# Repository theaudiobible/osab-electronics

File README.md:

## OSAB - the Open Source Audio Bible player
## [theaudiobible.org](http://theaudiobible.org/)
#### Copyright (C) 2011-2022 Theophilus

OSAB is a design for a portable audio Bible player released under the MIT Licence in the hope that it will be used by others worldwide to produce and distribute portable audio players that are specifically designed to share God's word with those who need to hear.

The intention is to share firmware, software, schematics, PCB layout and enclosure design along with instructions on how to put it all together.  The intention with the enclosure is that it be 3D-printable on a low cost FDM 3D printer, or mass-producible via injection moulding.

## osab-electronics
This is the repository for the EDA files for OSAB.

### Dependencies
- The schematic and PCB design tool is [KiCad](http://kicad.org/)
- [meshconv](https://www.patrickmin.com/meshconv/) is used to convert the VRML file to STL for use in OpenSCAD for the enclosure design.

### Generate STL file
To generate `osab.stl` for inclusion in the `osab-enclosure/osab.stl` soft link:
1. Open `osab.kicad_pcb` in KiCad Pcbnew.
2. Click `File` > `Export` > `VRML`.
3. Set these options:
   - `Coordinate origin options`: `User defined origin`
   - `User defined origin`:
      - `Units`: `mm`
      - `X`: `150`
      - `Y`: `100`
   - `VRML Units for Output Files`: `mm`
4. Click `OK`.  The output file should be `osab.wrl`.
5. Quit Pcbnew.
6. Download `meshconv` from https://www.patrickmin.com/meshconv/
7. Put meshconv somewhere in your PATH:
   `sudo chown root.root meshconv`
   `sudo chmod 755 meshconv`
   `sudo mv meshconv /usr/local/bin`
8. Convert the VRML file to STL as follows:
   `meshconv osab.wrl -c stl`
9. The output file `osab.stl` should be in the `osab-electronics` directory - there is a soft link from `osab-enclosure/osab.stl` to this file for inclusion in `osab-enclosure/osab-enclosure.scad`.

### Licence
This is open source hardware released under the MIT Licence - please see the LICENCE file in this directory.

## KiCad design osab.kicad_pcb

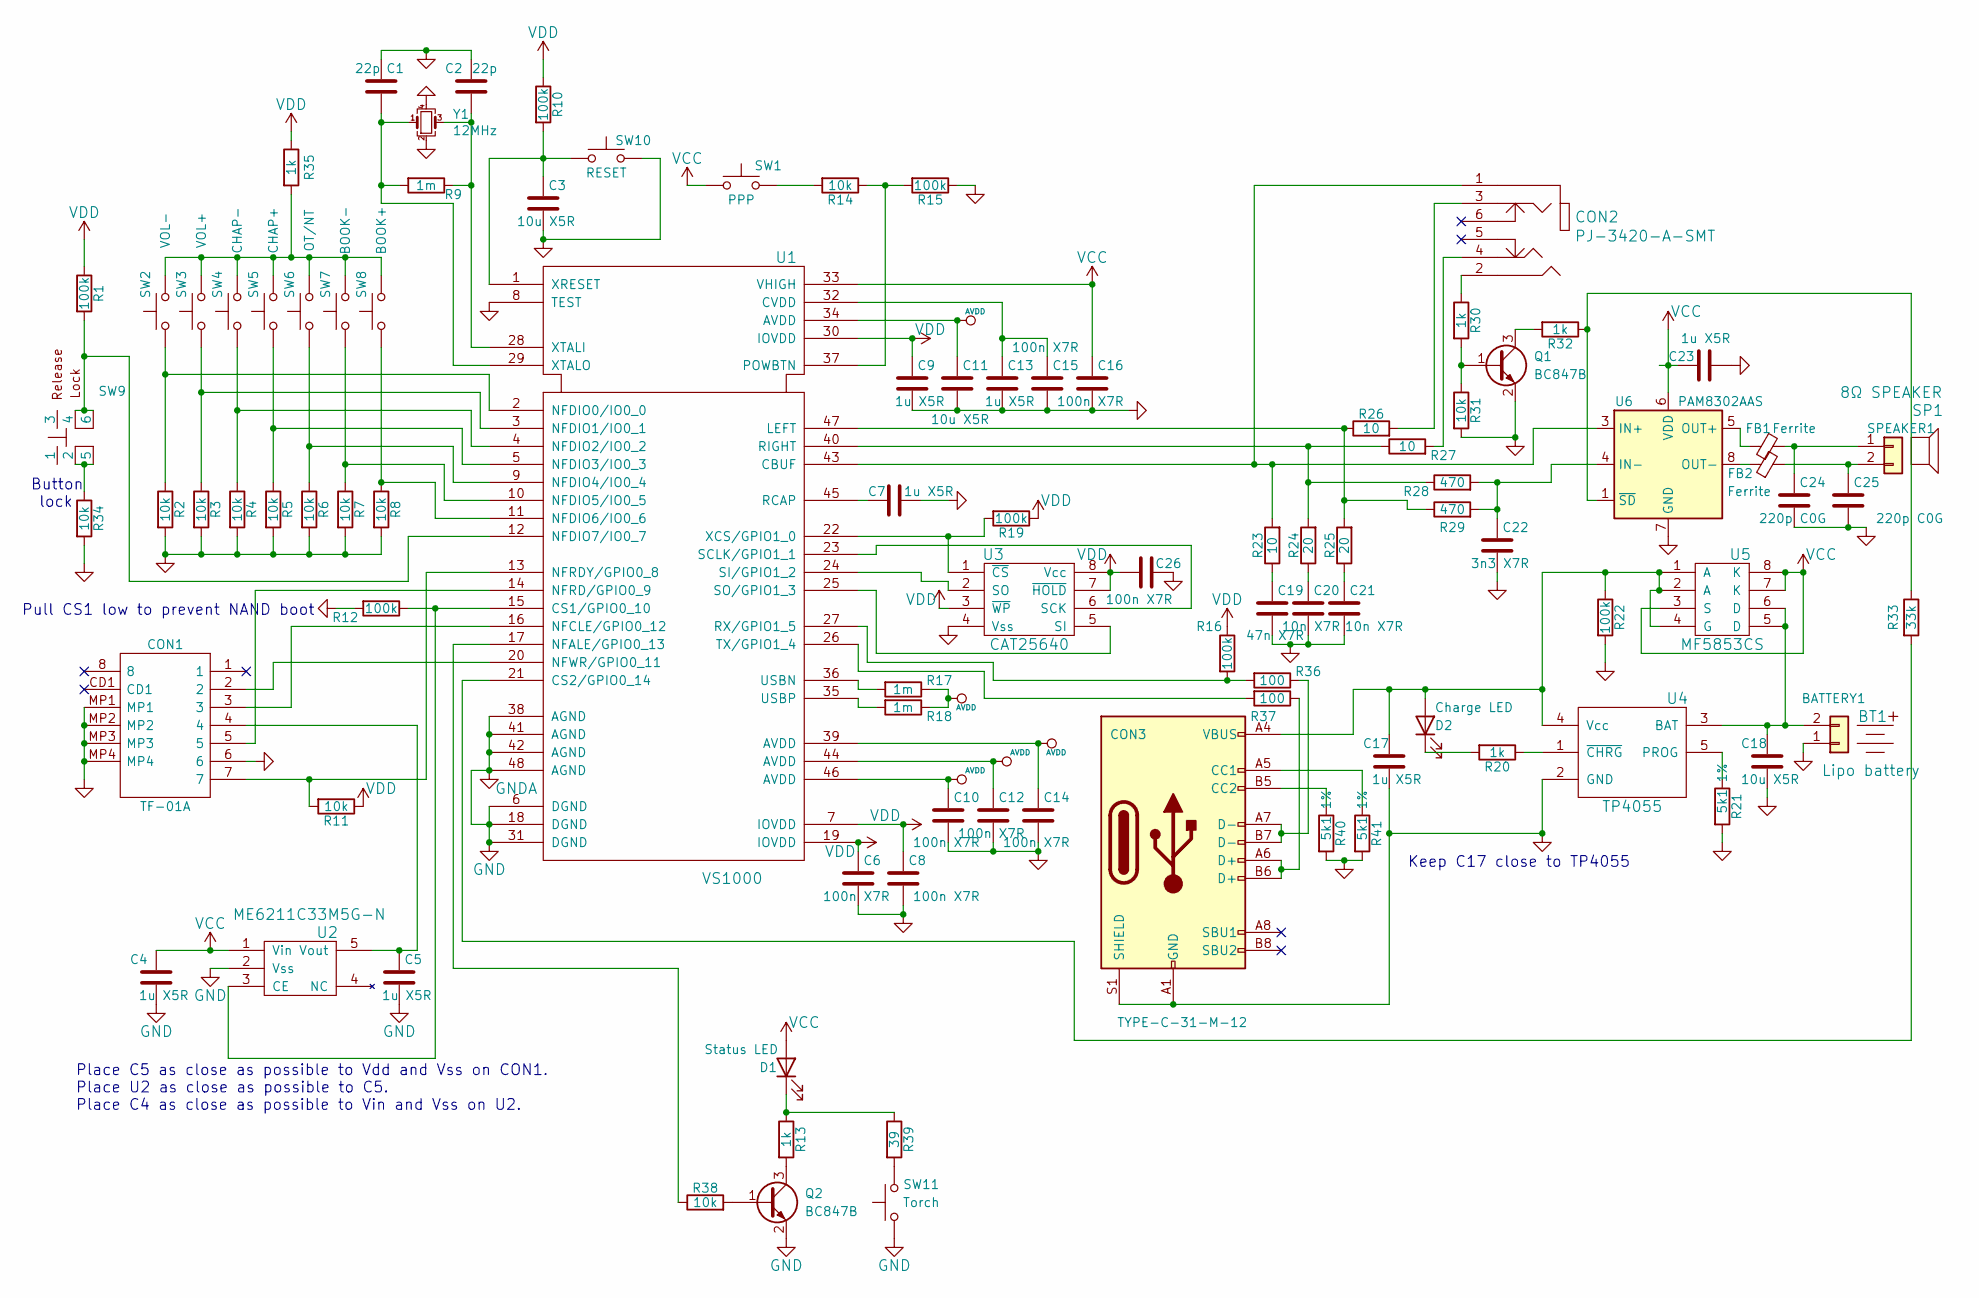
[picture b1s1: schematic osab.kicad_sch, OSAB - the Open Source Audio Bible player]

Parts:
BATTERY1: Conn_01x02; JST_PH_S2B-PH-SM4-TB_1x02-1MP_P2.00mm_Horizontal; MPN KH-A2001WF-02A; LCSC C2688784
BT1: Lipo battery; NULL; MPN BZ 602030
C1, C2: 22p; C_0603_1608Metric; MPN CL10C220JB8NNNC; LCSC C1653
C3, C11, C18: 10u X5R; C_0603_1608Metric; MPN CL10A106KP8NNNC; LCSC C19702
C4, C5, C7, C9, C13, C17, C23: 1u X5R; C_0603_1608Metric; MPN CL10A105KB8NNNC; LCSC C15849
C6, C8, C10, C12, C14, C15, C16, C26: 100n X7R; C_0603_1608Metric; MPN CL10B104KB8NNNC; LCSC C1591
C19: 47n X7R; C_0603_1608Metric; MPN CL10B473KB8NNNC; LCSC C1622
C20, C21: 10n X7R; C_0603_1608Metric; MPN CL10B103KB8NNNC; LCSC C1589
C22: 3n3 X7R; C_0603_1608Metric; MPN CL10B332KB8NNNC; LCSC C1613
C24, C25: 220p C0G; C_0603_1608Metric; MPN CL10C221JB8NNNC; LCSC C27675
CON1: TF-01A; TF01A; Manufacturer_Part_Number TF-01A; LCSC C91145
CON2: PJ-3420-A-SMT; MPN PJ-3420-A-SMT; LCSC C319102
CON3: TYPE-C-31-M-12; USB_C_Receptacle_HRO_TYPE-C-31-M-12; MPN TYPE-C-31-M-12; LCSC C165948
D1: Status LED; 0805-LED; MPN MHS171WDT-C2; LCSC C693902
D2: Charge LED; 0602-LED; MPN LTST-S270KRKT; LCSC C125114
FB1, FB2: Ferrite; R_0603_1608Metric; MPN MMZ1608Y152BTA00; LCSC C275454
Q1, Q2: BC847B; SOT-23; MPN BC847BLT1G; LCSC C94393
R1, R10, R12, R15, R16, R19, R22: 100k; R_0603_1608Metric; MPN ARG03FTC1003; LCSC C217682
R2, R3, R4, R5, R6, R7, R8, R11, R14, R31, R34, R38: 10k; R_0603_1608Metric; MPN ARG03FTC1002; LCSC C217687
R9, R17, R18: 1m; R_0603_1608Metric; MPN AR03FTC1004; LCSC C234360
R13, R20, R30, R32, R35: 1k; R_0603_1608Metric; MPN ARG03FTC1001; LCSC C217840
R21, R40, R41: 5k1 1%; R_0603_1608Metric; MPN ARG03FTC5101; LCSC C218090
R23, R26, R27: 10; R_0603_1608Metric; MPN ARG03FTC0100; LCSC C217691
R24, R25: 20; R_0603_1608Metric; MPN ARG03FTC0200; LCSC C217873
R28, R29: 470; R_0603_1608Metric; MPN ARG03FTC4700; LCSC C218042
R33: 33k; R_0603_1608Metric; MPN ARG03FTC3302; LCSC C217971
R36, R37: 100; R_0603_1608Metric; MPN ARG03FTC1000; LCSC C217683
R39: 39; R_0603_1608Metric; MPN 0603WAF390JT5E; LCSC C23154
SP1: 8Ω SPEAKER; NULL; MPN 28M03-8T-H52-L70; LCSC C391017
SPEAKER1: Conn_01x02; WAFER-125W-2P; MPN WAFER-125W-2P; LCSC C2840410
SW1: PPP; SW_SPST_TL3342; MPN K2-1187SQ-A4SW-06; LCSC C92584
SW2: VOL-; SW_SPST_TL3342; MPN K2-1187SQ-A4SW-06; LCSC C92584
SW3: VOL+; SW_SPST_TL3342; MPN K2-1187SQ-A4SW-06; LCSC C92584
SW4: CHAP-; SW_SPST_TL3342; MPN K2-1187SQ-A4SW-06; LCSC C92584
SW5: CHAP+; SW_SPST_TL3342; MPN K2-1187SQ-A4SW-06; LCSC C92584
SW6: OT/NT; SW_SPST_TL3342; MPN K2-1187SQ-A4SW-06; LCSC C92584
SW7: BOOK-; SW_SPST_TL3342; MPN K2-1187SQ-A4SW-06; LCSC C92584
SW8: BOOK+; SW_SPST_TL3342; MPN K2-1187SQ-A4SW-06; LCSC C92584
SW9: XKB5858-Z-F; MPN XKB5858-Z-F; LCSC C780036
SW10: RESET; SW_SPST_TL3342; MPN K2-1187SQ-A4SW-06; LCSC C92584
SW11: Torch; SW_SPST_TL3342; MPN K2-1187SQ-A4SW-06; LCSC C92584
U1: VS1000; LQFP-48_7x7mm_P0.5mm; MPN VS1000D-L; LCSC C486305
U2: ME6211C33M5G-N; SOT-23-5; MPN ME6211C33M5G-N; LCSC C82942
U3: CAT25640; SOIC-8_3.9x4.9mm_P1.27mm; MPN CAT25640VI-GT3; LCSC C153776
U4: TP4055; SOT-23-5; MPN TP4055; LCSC C28441
U5: MF5853CS; DFN8-2x3-0.65pitch; MPN MF5853CS; LCSC C375698
U6: PAM8302AAS; MSOP-8_3x3mm_P0.65mm; MPN PAM8302AASCR; LCSC C113367
Y1: 12MHz; Crystal_SMD_3225-4Pin_3.2x2.5mm; MPN X322512MSB4SI; LCSC C9002

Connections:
AVDD: C10.1, C11.1, C12.1, C14.1, R17.1, R18.1, U1.34 (AVDD), U1.39 (AVDD), U1.44 (AVDD), U1.46 (AVDD)
GND: BATTERY1.1, C1.1, C2.1, C3.2, C4.2, C5.2, C6.2, C7.1, C8.2, C9.2, C10.2, C11.2, C12.2, C13.2, C14.2, C15.2, C16.2, C17.2, C18.2, C19.2, C20.2, C21.2, C22.2, C23.2, C24.2, C25.2, C26.2, CON1.6, CON1.MP1, CON1.MP2, CON1.MP3, CON1.MP4, CON3.A1 (GND), CON3.A12 (GND), CON3.B1 (GND), CON3.B12 (GND), CON3.S1 (SHIELD), Q1.2 (E), Q2.2 (E), R2.2, R3.2, R4.2, R5.2, R6.2, R7.2, R8.2, R12.2, R15.1, R21.2, R22.2, R31.2, R34.2, R40.2, R41.2, SW10.1, SW11.1, U1.6 (DGND), U1.8 (TEST), U1.18 (DGND), U1.31 (DGND), U1.38 (AGND), U1.41 (AGND), U1.42 (AGND), U1.48 (AGND), U2.2 (Vss), U3.4 (Vss), U4.2 (GND), U6.7 (GND), Y1.2, Y1.4
unnamed: BATTERY1.2, C18.1, U4.3 (BAT), U5.5 (D), U5.6 (D)
unnamed: C1.2, R9.2, U1.29 (XTALO), Y1.1
unnamed: C2.2, R9.1, U1.28 (XTALI), Y1.3
unnamed: C3.1, R10.2, SW10.2, U1.1 (XRESET)
unnamed: C5.1, CON1.4, U2.5 (Vout)
unnamed: C7.2, U1.45 (RCAP)
unnamed: C13.1, C15.1, U1.32 (CVDD)
unnamed: C17.1, CON3.A4 (VBUS), CON3.A9 (VBUS), CON3.B4 (VBUS), CON3.B9 (VBUS), D2.2 (A), R22.1, U4.4 (Vcc), U5.1 (A), U5.2 (A), U5.4 (G)
unnamed: C19.1, R23.1
unnamed: C20.1, R24.1
unnamed: C21.1, R25.1
unnamed: C22.1, R28.2, R29.2, U6.4 (IN-)
unnamed: C24.1, FB1.2, SPEAKER1.1
unnamed: C25.1, FB2.2, SPEAKER1.2
unnamed: CON1.2, U1.20 (NFWR/GPIO0_11)
unnamed: CON1.3, U1.16 (NFCLE/GPIO0_12)
unnamed: CON1.5, U1.14 (NFRD/GPIO0_9)
unnamed: CON1.7, R11.2, U1.13 (NFRDY/GPIO0_8)
unnamed: CON2.1, R23.2, U1.43 (CBUF), U6.3 (IN+)
unnamed: CON2.2, R30.1
unnamed: CON2.3, R26.2
unnamed: CON2.4, R27.2
unnamed: CON3.A5 (CC1), R41.1
unnamed: CON3.A6 (D+), CON3.B6 (D+), R37.1
unnamed: CON3.A7 (D-), CON3.B7 (D-), R36.1
unnamed: CON3.B5 (CC2), R40.1
unnamed: D1.1 (K), R13.1, R39.1
unnamed: D2.1 (K), R20.2
unnamed: FB1.1, U6.5 (OUT+)
unnamed: FB2.1, U6.8 (OUT-)
unnamed: Q1.1 (B), R30.2, R31.1
unnamed: Q1.3 (C), R32.2
unnamed: Q2.1 (B), R38.2
unnamed: Q2.3 (C), R13.2
unnamed: R1.2, SW9.4, SW9.6, U1.12 (NFDIO7/IO0_7)
unnamed: R2.1, SW2.1, U1.2 (NFDIO0/IO0_0)
unnamed: R3.1, SW3.1, U1.3 (NFDIO1/IO0_1)
unnamed: R4.1, SW4.1, U1.4 (NFDIO2/IO0_2)
unnamed: R5.1, SW5.1, U1.5 (NFDIO3/IO0_3)
unnamed: R6.1, SW6.1, U1.9 (NFDIO4/IO0_4)
unnamed: R7.1, SW7.1, U1.10 (NFDIO5/IO0_5)
unnamed: R8.1, SW8.1, U1.11 (NFDIO6/IO0_6)
unnamed: R12.1, U1.15 (CS1/GPIO0_10), U2.3 (CE)
unnamed: R14.1, R15.2, U1.37 (POWBTN)
unnamed: R14.2, SW1.2
unnamed: R16.2, R36.2, U1.27 (RX/GPIO1_5)
unnamed: R17.2, U1.36 (USBN)
unnamed: R18.2, U1.35 (USBP)
unnamed: R19.2, U1.22 (XCS/GPIO1_0), U3.1 (~CS)
unnamed: R20.1, U4.1 (~CHRG)
unnamed: R21.1, U4.5 (PROG)
unnamed: R24.2, R27.1, R28.1, U1.40 (RIGHT)
unnamed: R25.2, R26.1, R29.1, U1.47 (LEFT)
unnamed: R32.1, R33.1, U6.1 (~SD)
unnamed: R33.2, U1.21 (CS2/GPIO0_14)
unnamed: R34.1, SW9.2, SW9.5
unnamed: R35.2, SW2.2, SW3.2, SW4.2, SW5.2, SW6.2, SW7.2, SW8.2
unnamed: R37.2, U1.26 (TX/GPIO1_4)
unnamed: R38.1, U1.17 (NFALE/GPIO0_13)
unnamed: R39.2, SW11.2
unnamed: U1.23 (SCLK/GPIO1_1), U3.6 (SCK)
unnamed: U1.24 (SI/GPIO1_2), U3.2 (SO)
unnamed: U1.25 (SO/GPIO1_3), U3.5 (SI)
VCC: C4.1, C16.1, C23.1, D1.2 (A), SW1.1, U1.33 (VHIGH), U2.1 (Vin), U5.3 (S), U5.7 (K), U5.8 (K), U6.6 (VDD)
VDD: C6.1, C8.1, C9.1, C26.1, R1.1, R10.1, R11.1, R16.1, R19.1, R35.1, U1.7 (IOVDD), U1.19 (IOVDD), U1.30 (IOVDD), U3.3 (~WP), U3.7 (~HOLD), U3.8 (Vcc)

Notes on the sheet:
Button lock
Pull CS1 low to prevent NAND boot
Place C5 as close as possible to Vdd and Vss on CON1. Place U2 as close as possible to C5. Place C4 as close as possible to Vin and Vss on U2.
Keep C17 close to TP4055

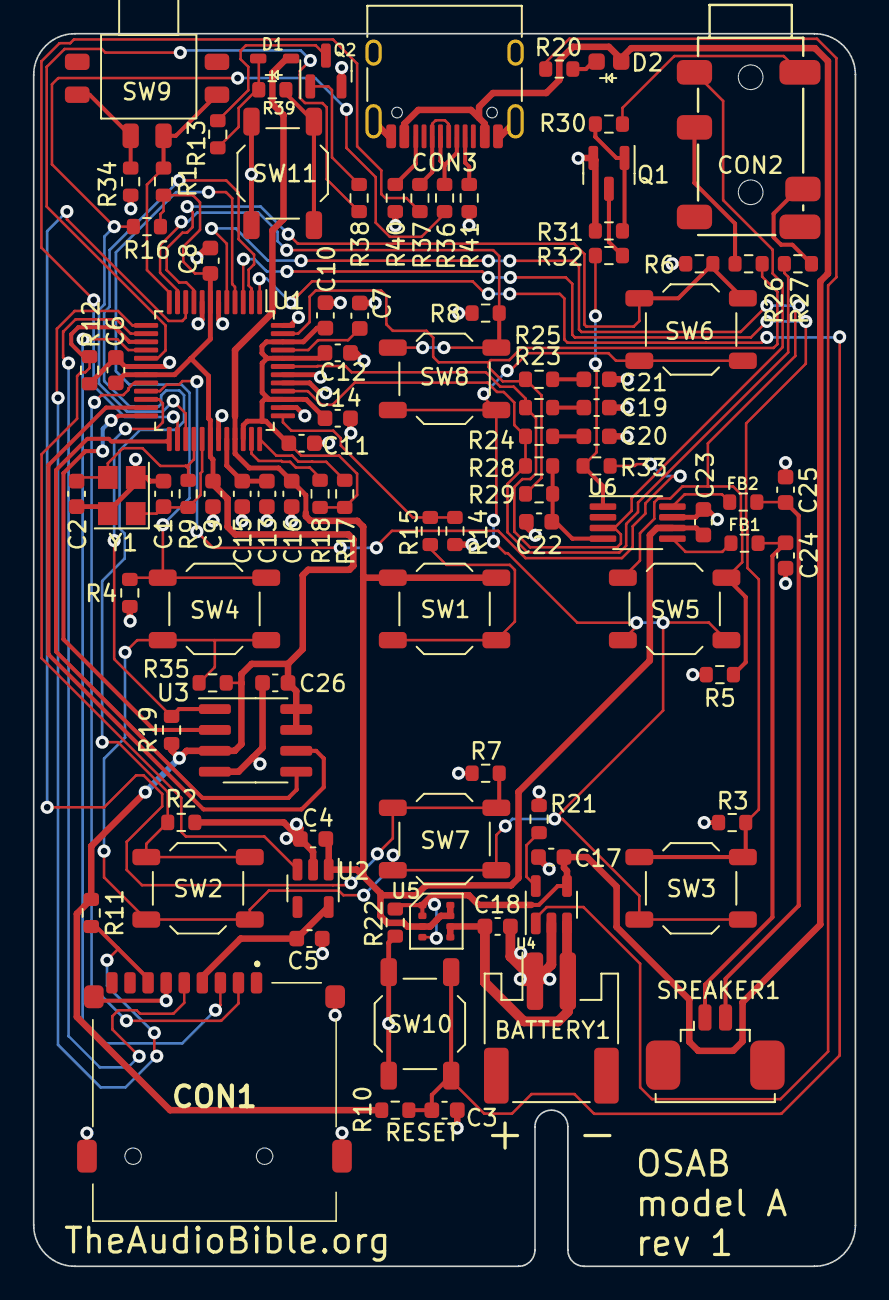
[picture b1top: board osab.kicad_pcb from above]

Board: 2 copper layers, 50.0 x 75.0 mm, 98 parts (0 on the bottom side), 67 nets.

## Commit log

2018-08-12 Initial commit.
2018-08-12 Ignore osab-rescue.lib
2019-08-07 Changed all rescue symbols to their appropriate libraries
    Got rid of some superfluous? files
    Reorganised directory structure of libraries
    Kicad seems to have changed some refs
    Changed all X5R caps to X7R
    Updated board rev
    kicad-5: Changed footprints from 0603 to 0805 for hand soldering
2020-02-15 Comitting updates without zero ohm resistors to make a good point to branch multi-layer boards
    usb-c: Swapped microB for Korean-Hroparts TYPE-C-31-M-12
    usb-c: Multiple collapsed/consolidated changes
    usb-c: Added SamacSys model for TF-01A
    usb-c: A multitude of changes
    usb-c: Various changes
    usb-c: Various changes
2020-02-17 single-sided: PCB routing updates
2020-02-29 single-sided: Completed routing all non-GND tracks
2020-02-29 single-sided: Completed routing all tracks, including GND
2020-02-29 single-sided: Pushed earphone and USB connectors out a bit further
2020-03-04 single-sided: Placement of labels on silkscreen
2020-03-05 single-sided: Refilled back layer
2020-03-05 single-sided: Added filled zone for front copper connected to no net
2020-03-06 single-sided: Added OSAB labelling on front silkscreen
2020-03-07 single-sided: Added 3D model for PJ-3420 3.5mm audio socket
2020-03-07 single-sided: Updated PJ-3420 on ssb
2020-03-08 single-sided: Moved earphone and USB sockets back a bit
2020-03-08 single-sided: Nudged USB socket out by 0.2 mm
2020-03-12 single-sided: Moved button lock back 5.75 mm
2020-03-29 single-sided: Added mounting holes
2020-04-18 single-sided: Got rid of mounting holes at the top
2020-04-18 single-sided: Saving plotting options
2020-05-02 single-sided: Increased mounting hole diameter from 1.5 to 2.5 mm
2020-05-02 single-sided: Increased mounting hole diameter from 2.5 to 3.0 mm
2020-05-02 single-sided: Added NPTH-2.5 and NPTH-3.0 to OSAB footprint library
2020-08-01 Changed website
2020-08-02 Changed website in master branch
2020-08-08 single-sided: Instructions to generate STL file for osab-enclosure
2021-11-08 Update README.md
    https://forum.kicad.info/t/warning-avoid-all-links-to-kicad-pcb-org-use-kicad-org/31521
2022-02-09 production: C1,C2 -> 0603
2022-02-09 production: C3,C11,C18 10u -> 0603
2022-02-09 production: C4,C5,C7,C9,C13,C17,C23 1u -> 0603
2022-02-15 production: Changed all 0805 cap footprints to 0603
2022-02-16 production: 100n caps replaced with 0603 Samsung
2022-02-16 production: Changed MPNs for earlier cap changes
2022-02-16 production: Changed 1u from 10V to 50V
2022-02-16 production: 3n3 to 0603
2022-02-16 production: 47n to 0603
2022-02-16 production: 10n to 0603
2022-02-16 production: Changed all 0805 resistor footprints to 0603
2022-02-19 production: Changed all 10k resistors to 0603
2022-02-19 production: Changed all 100k resistors to 0603
2022-02-22 production: Changed 1m resistor to 0603
2022-02-23 production: Changed all 1k resistors to 0603
2022-02-23 production: Changed all 10R resistors to 0603
2022-02-23 production: Changed all 20R resistors to 0603
2022-02-23 production: Changed all 470R resistors to 0603
2022-02-23 production: Changed 5k1 resistor to 0603
2022-02-23 production: Changed all 100R resistors to 0603
2022-02-23 production: Changed 33k resistor to 0603
2022-02-23 production: Changed 25LC640A to CAT25640
2022-02-26 production: Replaced TCS7191 with PAM8302A
2022-02-26 production: New LEDs
2022-02-26 production: Button lock from sliding to push latch
2022-02-27 production: Actual speaker for which enclosure was designed
2022-02-27 production: Battery and speaker terminals to CAX SMD
2022-02-27 production: Revert U3 to osab:25LC640A to keep Kicad happy
2022-03-06 production: Kicad 6 project and schematic files
2022-03-06 production: Got rid of Kicad 5 project and schematic files
2022-03-06 production: Torch; ferrite beads
2022-03-07 production: Added alternate battery
2022-03-07 production: Changed USB resistors from 100k to 1m as per datasheet
2022-03-07 production: Removed short between pins 25 and 27 of U1
2022-04-02 production: 4.5V alkalike alternate battery
2022-04-19 production: Added CC pulldowns for USB-C and NCs where needed
2022-04-19 production: Changed JST-type connectors
2022-04-19 production: Button lock footprint
2022-04-19 production: JLCPCB board constraints + removed eeprom boot footprint
2022-05-16 production: 50 mm wide PCB before laying traces
2022-05-16 production: rotated VS1000 90 clockwise to trace analogue better
2022-05-17 production: Locked footprints that should not move
2022-05-17 production: Locked edge courtyards
2022-05-21 production: Changed speaker + conn for speaker; Added GND plane splits for GNDA
2022-05-21 production: Better placement of amp and battery chips
2022-05-28 production: Rounded corners and added slot for wires
2022-05-30 production: Routed analog tracks
2022-05-30 production: Routed crystal
2022-05-31 production: Added C26 for eeprom; routing tracks
2022-05-31 production: Routed charge diode
2022-05-31 production: Routing tracks...
2022-06-02 production: 0 unrouted
2022-06-02 production: DRC fixes
2022-06-03 production: Added LCSC references
2022-06-03 production: Text layout
2022-06-03 production: Text layout on f.silk and f.fab
2022-06-03 production: Passed DRC
2022-06-04 production: Changed AVDD cap layout
2022-06-04 production: Shorter bridge
2022-06-04 production: Added footprint for speaker connector
2022-06-04 production: Corrected battery polarity
2022-06-04 production: Final commit after generating outputs
2022-06-05 production: New status LED and speaker connector
2022-06-05 production: New status LED and speaker connector + footprints
2022-06-06 Production into master for OSAB model A rev 1 (#2)
    * production: C1,C2 -> 0603
    * production: C3,C11,C18 10u -> 0603
    * production: C4,C5,C7,C9,C13,C17,C23 1u -> 0603
    * production: Changed all 0805 cap footprints to 0603
    * production: 100n caps replaced with 0603 Samsung
    * production: Changed MPNs for earlier cap changes
2022-07-13 production: Updated README to use meshconv
2022-07-13 production: Updated README to use meshconv (#3)
2022-07-22 prod-1: Added 3D model for USB-C
2022-07-23 prod-1: Added STEP model for XKB5858-Z-F button lock from traceparts.com
2022-12-11 prod-1: Added 3D/xkb5858-z-f.stp to .gitignore

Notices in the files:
osab.kicad_sch:
Licence: See LICENCE file in osab-electronics project directory
